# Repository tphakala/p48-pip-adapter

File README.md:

# P48 → 8 V PIP adapter (fits inside an XLR connector)

An ultra-compact **phantom-power (24-48 V) to 8 V plug-in-power (PIP)** adapter
board for high-sensitivity electret condenser capsules such as the PUI Audio
**AOM-5024**. The whole circuit lives on a **11.1 × 35.3 × 0.8 mm** four-layer
PCB thin enough to slip *between* the pins of a Neutrik **NC3MXX** male XLR and
solder to them directly, so a two-wire electret becomes a self-contained,
buffered, impedance-balanced phantom mic with nothing hanging off the back. It
runs on standard phantom power from any mixer, audio interface (such as a
Focusrite Scarlett), or field recorder.

This is the active-electronics counterpart to the 3D-printed
[`aom5024-xlr`](https://github.com/tphakala/aom5024-xlr) pencil-mic housing.
That project runs the capsule on a bare resistor + capacitor (fine for short
cable runs); this board is the buffered, impedance-balanced front end it points
to for long cables and true common-mode rejection, squeezed onto a board that
still fits inside the connector.

> **Order the bare board as 0.8 mm thick.** The thin edge has to fit into the
> gap between the three Neutrik pins; a standard 1.6 mm board is far too thick.
> This is a deliberate, load-bearing spec, not a default you can ignore.

## How it works

The circuit is three parts, one per section below: a capacitance-multiplier
supply that cleans up the phantom rail, a matched pair of Class-A buffers that
drive the cable, and a current split that keeps the DC draw equal on both
phantom pins.

### 1. Power supply: capacitance multiplier

Rather than running the capsule off a noisy Zener directly, the supply is a
**capacitance multiplier**:

- Phantom power is tapped equally from XLR pins 2 and 3.
- An 8.2 V Zener (D1) sets a raw voltage reference.
- A large RC low-pass (100 kΩ + 22 µF) puts the corner well below 1 Hz,
  scrubbing the Zener's avalanche noise off the reference.
- An NPN emitter follower (Q1) buffers that silent reference to the ~7.5 V
  PIP rail that biases the capsule.

### 2. Audio stage: impedance-balanced Class-A buffer

A two-wire electret can't produce a true differential signal on its own, so the
board fakes a balanced line the preamp can't tell from the real thing:

- **Pin 2 (hot)** is driven by a PNP emitter follower (Q2), a Class-A buffer
  that converts the capsule's high output impedance to a low ~78 Ω that
  drives long cable without treble roll-off.
- **Pin 3 (cold)** uses an identical PNP (Q3) with its base AC-grounded: no
  audio, but it matches Q2's ~78 Ω output impedance exactly.
- To the preamp this looks like a balanced source, so common-mode hum and RF
  cancel.

### 3. DC current balancing

The circuit pulls roughly **3 mA per pin**, a balanced DC draw that suits any
balanced input, whether electronically balanced (most audio interfaces and
modern preamps) or transformer-coupled: pin 2 feeds the hot buffer (Q2); pin 3
feeds the cold buffer (Q3) plus the regulator.

## Simulated performance

The circuit is verified headlessly in **ngspice**. The deck is generated from
[`netlist.py`](netlist.py), the same single source of truth as the board and
schematic, so the simulation can't drift from the hardware. `sim/run.ps1`
range-checks 17 design assertions; `sim/plot_response.py` sweeps the wide-band
response below (10 Hz – 384 kHz).

- **Flat through the audio band** at −0.56 dB (a near-unity buffer), driving a
  modelled ~30 m cable into a 2 kΩ preamp.
- **Flat well into the ultrasonic**: only ~0.6 dB down at **384 kHz** (the
  192 kHz Nyquist of a 384 kHz sample rate). The trace is referred to the
  capsule output node, so it shows the *adapter electronics in isolation*: with
  a wide-band capsule the circuit is not the bottleneck for ultrasonic work such
  as **bat-call recording**. (The stock AOM-5024 electret rolls off far earlier;
  swap it for an ultrasonic-capable capsule for that use.)
- **~78 Ω source impedance**, flat from the audio band into the ultrasonic, low
  enough to drive long cable without HF loss and to look benign to any balanced
  input.
- The **gentle sub-50 Hz roll-off** is the CB2/CB3 emitter bypass, and it is
  deliberate: some LF attenuation is desirable here and it keeps those bypass
  caps small.

See [`sim/README.md`](sim/README.md) for the harness and the full assertion list.

## The board

Four copper layers, everything on the **top** side for single-sided assembly.
The two inner layers are **solid ground planes**, a real on-board Faraday cage
for the µV front end, via-stitched to the outer ground pours and to the XLR
pin-1 ground, backing up the grounded zinc shell:

| Layer | Net / role |
| :-- | :-- |
| **F.Cu** | signal routing + all component placement, GND flood-fill |
| **In1.Cu** | solid ground plane (shield / image plane under the signal) |
| **In2.Cu** | solid ground plane (second reference for the back-side routing) |
| **B.Cu** | GND pour + the few signal escapes + the XLR pin-3 pad |

Signal routing is confined to the outer layers so the inner planes stay
unbroken; the supply nets (P2/P3/VPIP/VREF) use a wider 0.25 mm **Power**
netclass, while GND is distributed by the planes rather than as tracks.

### XLR sandwich mount

The thin board edge slides **between** the three NC3MXX pins (7.62 mm cup
spacing) and the pins solder to the board faces, pins 1 and 2 on the front and
pin 3 on the back:

| Pin | Net | Face | x (mm) |
| :-- | :-- | :-- | :-- |
| 1 | GND | front | 1.90 |
| 2 | hot | front | 9.52 |
| 3 | cold | back | 5.71 |

The three XLR pads are **8 mm long**: the internal Neutrik pin runs ~5 mm along
the board and the pad extends 3 mm past the pin tip so there's copper to hand-
solder to. The pin tip keeps ≥ 5 mm clearance to the nearest component; the
35.3 mm board length is *derived* from that constraint in `netlist.py`.

The board's thin edge slots straight **between** the three XLR pins (pins 1 & 2
against the front component face, pin 3 against the back), with the pad end
seated against the connector body and the mating pins left free for the preamp.

<sub>The bare pin insert is modelled at this board's actual XLR-pad positions
(from `netlist.py`) to show the sandwich mount; the Neutrik NC3MXX STEP is one
fused solid whose pins can't be isolated, so the pins are drawn to match.</sub>

## Schematic

The full circuit, drawn from [`netlist.py`](netlist.py), the single source of
truth. On the left, the capacitance-multiplier reference/regulator (D1 zener,
R9/C4 sub-1 Hz filter, Q1 emitter follower) produces the clean **VPIP** rail; R10
biases the capsule; and the two impedance-matched PNP emitter followers (Q2 hot,
Q3 cold) draw the balanced ~3 mA per phantom pin, each with its CBx/RBx emitter-
bypass network for the low-Z output. This figure is drawn directly from the same
netlist that synthesizes the board, so the two cannot disagree.

## Bill of materials

All parts are SMD to fit the 11.1 mm width. Component values are nominal
(derived from the architecture and standard P48→PIP practice) and may benefit
from bench tuning before a production run.

| Ref | Value | Package | Function |
| :-- | :-- | :-- | :-- |
| Q1 | MMBT3904 | SOT-23 | NPN, regulator emitter follower |
| Q2, Q3 | MMBT3906 | SOT-23 | PNP, hot / cold audio buffers |
| D1 | 8.2 V Zener | SOD-323 | voltage reference |
| C1, C2, C3 | 22 µF 50 V | 1206 | filtering / DC blocking |
| C4 | 47 µF 50 V | 1206 | VREF filter (sub-1 Hz corner) |
| C5 | 10 µF 16 V | 0805 | PIP rail bypass |
| CB2, CB3 | 22 µF 50 V X7R | 1206 | emitter bypass → low-Z output |
| R1 | 7.5 kΩ | 1206 | hot buffer emitter feed (thermal, 1206) |
| R2 | 10 kΩ | 1206 | cold buffer emitter feed (thermal, 1206) |
| R3, R4, R6, R7 | 100 kΩ | 0603 | bias dividers |
| R8 | 1 kΩ | 0603 | regulator base stopper |
| R9 | 47 kΩ | 0603 | VREF feed |
| R10 | 6.8 kΩ | 0603 | mic bias |
| RB2, RB3 | 47 Ω | 0603 | emitter-bypass series stopper (cable stability) |

R1/R2 are **1206** (not 0603): each dissipates continuously inside the sealed
XLR shell, and 1206's 250 mW rating keeps a comfortable margin at 80 °C ambient.
CB2/CB3 sit across ~23 V DC, so they **must be 50 V rated** (X7R). There is
intentionally **no R5**. The full derived netlist (the single source of truth)
lives in [`netlist.py`](netlist.py) and is documented in [SPEC.md](SPEC.md); the
board is synthesized from it (schematic-free) and the schematic figure above is
drawn from the same netlist, so they cannot disagree.

## Manufacturing status

- **4-layer, 11.1 × 35.3 × 0.8 mm**, all parts top-side (single-sided assembly).
- **DRC: 0 errors, 0 unconnected pads, 0 footprint errors** (`kicad-cli pcb drc`).
- Track 0.15 mm (0.25 mm on the Power netclass), clearance 0.125 mm, vias
  0.6 / 0.3 mm, copper-to-edge ≥ 0.25 mm, solid In1/In2 ground planes with GND
  via stitching, all within JLCPCB / PCBWay standard 4-layer capability.
- Fab package: Gerber X2 + Excellon drill (PTH/NPTH separated) in
  [`Gerbers_PCBWay/`](Gerbers_PCBWay), zipped as `P48_Adapter_PCBWay.zip`.

**Known trade-off.** At 11.1 mm wide with six 1206 caps and two 1206 resistors,
the KiCad *courtyards* (assembly keep-out margins, ~4.7 mm for a 1206) unavoidably
overlap. There are no copper shorts (pad-to-pad clearance is fully enforced), so
the `courtyards_overlap` rule is downgraded to a warning. To remove it entirely,
move the 1206 parts to smaller packages or widen the board. Silkscreen reference
designators are hidden (illegible at this density); use the BOM and placement
data for assembly.

## Mechanical fit test

Before committing to a fab run, print `fit_test/p48_fittest.stl` and check the
board actually fits inside your connector. It's a single manifold solid: the
exact 0.8 mm outline, capsule through-holes, every component embossed at true
body size and height, raised solder pads, and the three long flat XLR solder
pads running along the board from the connector edge. Print flat, components up.

### Soldering to the connector

The board mounts as a sandwich between the Neutrik pins: pins 1 and 2 solder to
the front face, pin 3 to the back. Verified geometry (official KiCad Neutrik
NC3FAAV footprint, corroborated by the printed fit test): pins 1 and 2 are
coplanar and 7.62 mm apart; pin 3 is centred 4.45 mm off their plane. With the
~3 mm solder cups and the 0.8 mm board, pin 3 clears by only ~1.4 mm (about
0.6 mm of total slack), so when the board is seated flush against pins 1 and 2,
the pin-3 cup sits roughly 0.5 to 0.7 mm off its back-face pad and needs a
deliberately fat fillet to bridge the gap.

Solder in this order:

1. **Pre-tin** the pin-3 back-face pad **and** the pin-3 solder cup separately.
2. Seat the board flush against pins 1 and 2 and **solder those two joints
   first**: they set the board position.
3. **Bridge pin 3 last**, reflowing both pre-tinned surfaces into one fat fillet
   across the ~0.6 mm gap.

Soldering pins 1 and 2 before pin 3 keeps the board from being stressed while
it is wedged between the cups.

## Automated build pipeline

The whole board is generated headlessly from `netlist.py`, with no manual KiCad
editing. Steps that touch `pcbnew` run under KiCad's bundled Python; the rest
run under any Python 3.

```bash
KPY="$LOCALAPPDATA/Programs/KiCad/10.0/bin/python.exe"

"$KPY" route.py            # build a pristine board + route it (build_pcb + Freerouting)
python export_gerbers.py   # Gerbers + drill -> Gerbers_PCBWay/ + zip
python gen_fittest.py      # 3D-printable fit-test STL
python scripts/render_previews.py   # regenerate the images/ previews
```

- **`build_pcb.py`**: schematic-free board synthesis. Loads standard + custom
  (XLR / capsule) footprints, assigns every pad to its net, sets the 4-layer
  stackup, the Power netclass and design rules, draws the outline, places all
  parts with a collision-checked parametric auto-placer (two columns, all
  top-side), lays the solid In1/In2 GND planes and pours, and drops the GND
  stitch + pad-fanout via grid.
- **`route.py`**: regenerates a pristine board, exports a Specctra DSN,
  **relabels the inner layers as plane layers** so signal routing stays on the
  outer copper and the GND planes stay unbroken, runs **Freerouting fully
  headless** (`-Djava.awt.headless=true` + `gui.enabled=false`, no window ever
  opens), imports the routes with a built-in SES parser, then floods F.Cu/B.Cu
  with GND and refills. Result: 100 % routed, 0 unconnected.
- **`export_gerbers.py`**: Gerber X2 + Excellon via `kicad-cli`, zipped for fab.
- **`gen_fittest.py`**: extracts the routed geometry into the fit-test STL.
- **`scripts/render_previews.py`**: the preview images above, from the board
  (kicad-cli raytracer) and the fit-test STL (Blender).
- **`scripts/render_connector.py`**: the sandwich-mount render. Exports the
  board to GLB and renders it in Blender between three modelled gold pins placed
  at the board's real XLR-pad positions (no third-party connector model needed).
- **`scripts/gen_schematic.py`**: the wired schematic figure, drawn from
  `netlist.py` with schemdraw (SVG → WebP via Inkscape). This is the schematic
  of record: the board is synthesized directly from the netlist, so there is no
  separate hand-drawn KiCad schematic to fall out of sync.

### Toolchain

Built with **KiCad 10**, `kicad-cli`, **Freerouting**, **Blender** (previews)
and **OpenSCAD** (fit-test model). Tool paths in the scripts are set for the
author's Windows install (`route.py`, `export_gerbers.py`); adjust them, or set
the `KICAD_CLI` / `BLENDER` environment variables the render script reads, for
your own machine.

## Design notes

Dimensional provenance, the full derived netlist, and the reasoning behind the
placement and design rules live in [SPEC.md](SPEC.md).

## License

[CC BY-NC 4.0](LICENSE) (Creative Commons Attribution-NonCommercial). You are
free to build, modify and share this design with attribution.
**Commercial use is not permitted.** Do not sell this board, assembled units,
or derivatives of the design.

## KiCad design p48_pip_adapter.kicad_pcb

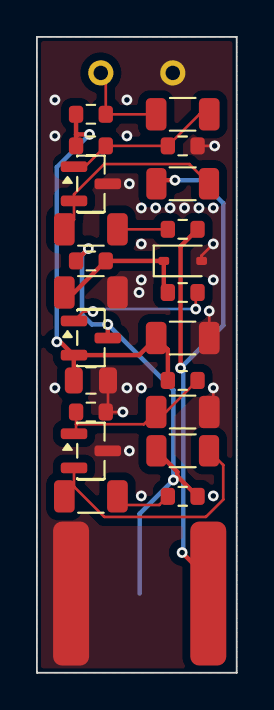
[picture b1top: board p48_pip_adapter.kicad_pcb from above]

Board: 4 copper layers, 11.1 x 35.3 mm, 24 parts (0 on the bottom side), 13 nets.

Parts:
C1, C2, C3: 22uF; C_1206_3216Metric
C4: 47uF; C_1206_3216Metric
C5: 10uF; C_0805_2012Metric
CB2, CB3: 22uF; C_1206_3216Metric
D1: 8.2V; D_SOD-323
J1: XLR3
MIC1: AOM5024
Q1: MMBT3904; SOT-23
Q2, Q3: MMBT3906; SOT-23
R1: 7.5k; R_1206_3216Metric
R2: 10k; R_1206_3216Metric
R3, R4, R6, R7: 100k; R_0603_1608Metric
R8: 1k; R_0603_1608Metric
R9: 47k; R_0603_1608Metric
R10: 6.8k; R_0603_1608Metric
RB2, RB3: 47; R_0603_1608Metric

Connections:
GND: C1.2, C3.2, C4.2, C5.2, D1.2, J1.1, MIC1.2, Q2.3, Q3.3, R4.2, R7.2
MICOUT: C2.1, MIC1.1, R10.2
NB2: CB2.2, RB2.1
NB3: CB3.2, RB3.1
P2: J1.2, R1.1, RB2.2
P3: J1.3, Q1.3, R2.1, R9.1, RB3.2
Q1B: Q1.1, R8.2
Q2B: C2.2, Q2.1, R3.2, R4.1
Q2E: CB2.1, Q2.2, R1.2
Q3B: C3.1, Q3.1, R6.2, R7.1
Q3E: CB3.1, Q3.2, R2.2
VPIP: C1.1, C5.1, Q1.2, R3.1, R6.1, R10.1
VREF: C4.1, D1.1, R8.1, R9.2
